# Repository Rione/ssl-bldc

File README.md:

# Ri-one BLDC Driver V1

|  | IC |
| --- | --- |
| MOSFET | [SIZ254DT-T1-GE3](https://www.mouser.jp/ProductDetail/Vishay-Siliconix/SIZ254DT-T1-GE3?qs=pUKx8fyJudCKVjpWQE2G2A%3D%3D) |
| MCU | [STM32F446RET6](https://jp.rs-online.com/web/p/microcontrollers/1106621) |
| Gate Driver | [DVR8300DRGER](https://www.ti.com/product/DRV8300/part-details/DRV8300DRGER) |
| CAN Transceiver | [TJA1441AT](https://akizukidenshi.com/catalog/g/gI-17464/) |
| Shunt Resistor| 10mΩ | 
| 3.3V Regulator | [AP7333-33SAG](https://akizukidenshi.com/catalog/g/gI-11360/) |
| Motor | [EC 45 flat 30W](https://www.maxongroup.com/medias/sys_master/root/8846629470238/20-JP-285.pdf)|

---

初めて作ったモータドライバ基板です．
記事も書いたので，良かったら見てください．
[tomixrm 初のモタドラ設計！！ゲート抵抗を計算して求めてみた](https://tomixrm.vercel.app/2e7cb67096e143f2a43334a63c00d47e)

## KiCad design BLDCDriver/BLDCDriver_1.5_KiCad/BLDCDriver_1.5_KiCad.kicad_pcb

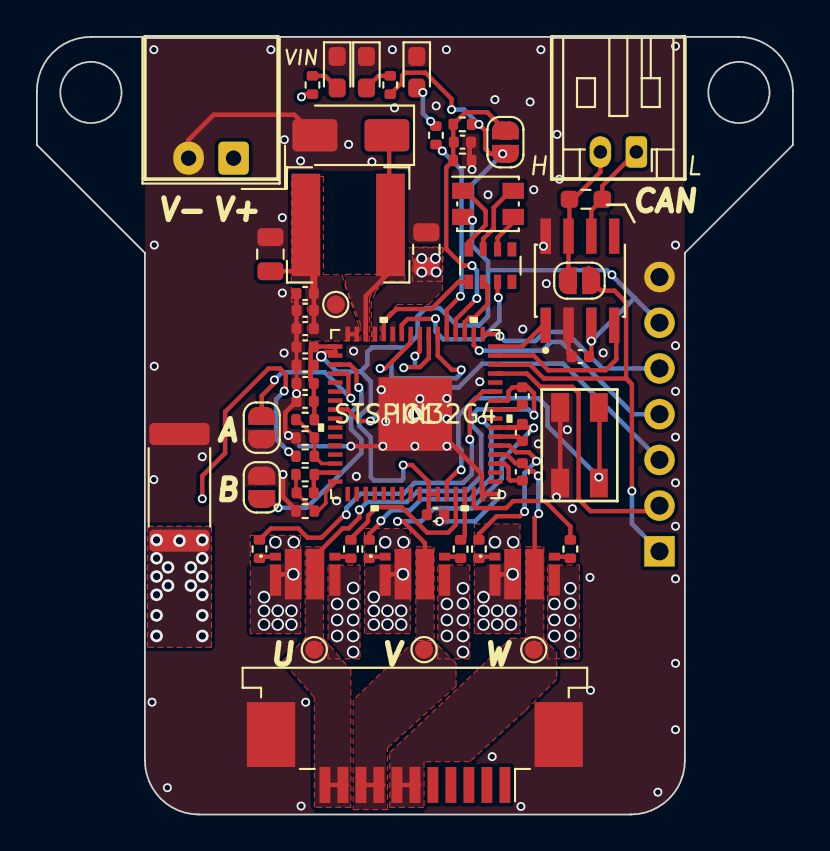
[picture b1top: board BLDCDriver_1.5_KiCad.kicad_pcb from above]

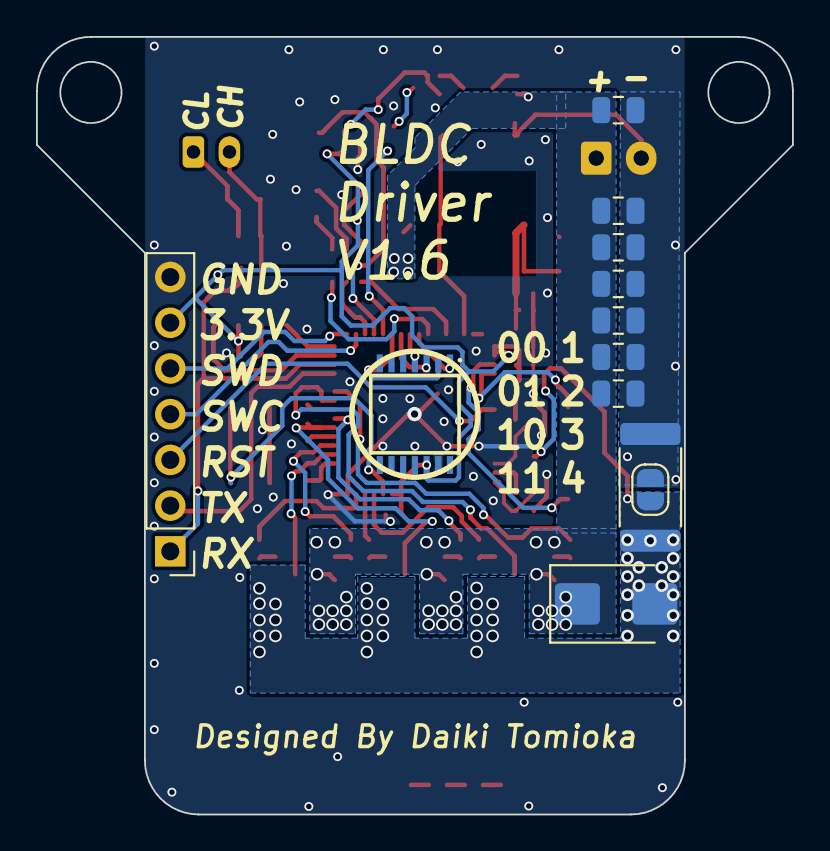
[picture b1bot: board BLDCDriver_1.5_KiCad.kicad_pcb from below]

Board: 2 copper layers, 42.0 x 43.2 mm, 70 parts (12 on the bottom side), 54 nets.

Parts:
C1, C2, C9, C17, C18, C19, C20: 22uF; C_0805_2012Metric
C3, C5, C7: 10uF; C_0402_1005Metric
C4, C6, C8, C25, C26: 100nF; C_0402_1005Metric
C10: 220nF; C_0805_2012Metric
C11, C12, C13, C14, C15, C16: 1uF; C_0402_1005Metric
C24: 10uf 25v; C_0805_2012Metric
D1: SS210; D_SMA
D2: LED_RGBA; LED_Kingbright_AAA3528ESGCT
D3: LED_Blue; LED_0603_1608Metric_Pad1.05x0.95mm_HandSolder
D4: LED_Pink; LED_0603_1608Metric_Pad1.05x0.95mm_HandSolder
D5: LED_White; LED_0603_1608Metric_Pad1.05x0.95mm_HandSolder
IC1: STSPIN32G4
J2: Debug; PinHeader_1x07_P2.54mm_Vertical
J3: FFC_11P_1mm; TE_1-84952-1_1x11-1MP_P1.0mm_Horizontal
J4: POWER; Molex_SPOX_5268-02A_1x02_P2.50mm_Horizontal
J5: CAN; JST_PH_S2B-PH-K_1x02_P2.00mm_Horizontal
JP1, JP2, JP3, JP4, JP5: Jumper_2_Open; SolderJumper-2_P1.3mm_Open_RoundedPad1.0x1.5mm
L1: 18uh; L_Bourns-SRN6028
R1, R14, R15: 22k; R_0402_1005Metric
R2, R11: 10k; R_0402_1005Metric
R4, R5, R6, R7, R8, R9: 51; R_0402_1005Metric
R10, R19: 4mΩ; R_2512_6332Metric
R12, R13, R16: 1.5k; R_0402_1005Metric
R17, R18: 1k; R_0402_1005Metric
R20: 120; R_0603_1608Metric_Pad0.98x0.95mm_HandSolder
RN1: 1k; R_Array_Convex_4x0603
SW1: SW_Push; SKRPACE010
TP1, TP2, TP3, TP4: TestPoint_Small; TestPoint_Pad_D1.0mm
TVS1: 16V; D_SMB
U1, U2, U3: SIZ254DTT1GE3
U5: AS5048A-HTSP-500; AS5048A_SOP65P640X120-14N
U7: MAX3051ESA_; SOIC127P600X175-8N

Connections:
BOOT1: C11.2, IC1.41 (BOOT1)
BOOT2: C13.2, IC1.38 (BOOT2)
BOOT3: C14.2, IC1.35 (BOOT3)
CANH: J5.2, JP5.1 (A), R20.1, U7.7 (CANH)
CANL: J5.1, R20.2, U7.6 (CANL)
CAN_RD: IC1.47 (PA11), U7.4 (RXD)
CAN_TD: IC1.48 (PA12), U7.1 (TXD)
GHS1: IC1.43 (GHS1), R4.1
GHS2: IC1.40 (GHS2), R6.1
GHS3: IC1.37 (GHS3), R8.1
GLS1: IC1.29 (GLS1), R5.1
GLS2: IC1.30 (GLS2), R7.1
GLS3: IC1.31 (GLS3), R9.1
GND: C1.1, C2.1, C3.2, C4.2, C5.2, C6.2, C7.2, C8.2, C9.1, C10.1, C12.2, C15.1, C17.1, C18.1, C19.1, C20.1, C24.2, C25.2, C26.2, D1.2 (A), D3.1 (K), D4.1 (K), D5.1 (K), IC1.32 (PGND), IC1.59 (PB8), IC1.65 (VSS), J2.7, J3.MP (MountPin), J4.2, JP2.2 (B), JP3.2 (B), JP4.2 (B), R2.2, R10.1, R13.1, R15.2, R19.1, SW1.1, U5.13 (GND), U7.2 (GND), U7.8 (RS)
GVCC_SW: D1.1 (K), IC1.62 (SW), L1.1
LED_Alive: IC1.53 (PD2), R18.1
LED_B: IC1.60 (PB9), RN1.5 (R4.2)
LED_G: IC1.51 (PA15), RN1.6 (R3.2)
LED_R: IC1.58 (PB7), RN1.7 (R2.2)
unnamed: D2.3 (BK), RN1.2 (R2.1)
unnamed: D2.2 (GK), RN1.3 (R3.1)
unnamed: D2.1 (RK), RN1.4 (R4.1)
unnamed: D3.2 (A), R11.2
unnamed: D4.2 (A), R17.2
unnamed: D5.2 (A), R18.2
unnamed: R4.2, U1.2 (G1)
unnamed: R5.2, U1.4 (G2)
unnamed: R6.2, U2.2 (G1)
unnamed: R7.2, U2.4 (G2)
unnamed: R8.2, U3.2 (G1)
unnamed: R9.2, U3.4 (G2)
OP_+1: IC1.14 (PA1), R12.2, R14.2, R15.1
OP_-1: C16.1, IC1.16 (PA3), R13.2, R16.1
OP_O1: C16.2, IC1.15 (PA2), R16.2
OUT1: C11.1, IC1.42 (OUT1), J3.10, J3.11, TP2.1, U1.3 (O)
OUT2: C13.1, IC1.39 (OUT2), J3.8, J3.9, TP3.1, U2.3 (O)
OUT3: C14.1, IC1.36 (OUT3), J3.6, J3.7, TP4.1, U3.3 (O)
SCREF: C12.1, IC1.52 (SCREF), JP1.1 (A), R1.2, R2.1
SHUNT_P1: JP2.1 (A), R10.2, R12.1, R19.2, TVS1.2 (A), U1.5 (S), U2.5 (S), U3.5 (S)
SPI1_CS: IC1.57 (PB6), U5.1 (~CSN)
SPI1_MISO: IC1.55 (PB4), U5.3 (MISO)
SPI1_MOSI: IC1.56 (PB5), U5.4 (MOSI)
SPI1_SCK: IC1.54 (PB3), U5.2 (CLK)
SW: IC1.28 (PB10), SW1.2
SWA: IC1.3 (PC13), JP3.1 (A)
SWB: IC1.4 (PC14), JP4.1 (A)
SWCLK: IC1.50 (PA14), J2.4
SWDIO: IC1.49 (PA13), J2.5
UART_RX: IC1.46 (PA10), J2.1, JP5.2 (B)
UART_TX: IC1.45 (PA9), J2.2
VCC: C7.1, C8.1, C24.1, C25.1, IC1.63 (VCC), IC1.64 (REGIN), L1.2, TP1.1
VD: C1.2, C2.2, C9.2, C10.2, C17.2, C18.2, C19.2, C20.2, IC1.61 (VM), J4.1, R11.1, TVS1.1 (K), U1.1 (D), U2.1 (D), U3.1 (D)
VDD: C3.1, C4.1, C5.1, C6.1, C15.2, C26.1, D2.4 (A), IC1.1 (REG3V3/VDD), IC1.2 (VBAT), IC1.26 (VREF+), IC1.27 (VDDA), J2.6, JP1.2 (B), R1.1, R14.1, R17.1, U5.12 (VDD3V), U7.3 (VCC)
nRST: IC1.8 (PG10), J2.3

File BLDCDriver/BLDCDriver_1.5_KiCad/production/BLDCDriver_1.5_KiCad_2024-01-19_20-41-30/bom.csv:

Designator,Footprint,Quantity,Value,LCSC Part #
"C1, C17, C18, C19, C2, C20, C9",0805,7,22uF,C338080
C10,0805,1,220nF,C107131
"C11, C12, C13, C14, C15, C16, C22",0402,7,1uF,C307413
"C21, C3, C5, C7",0402,4,10uF,C15525
"C23, C4, C6, C8",0402,4,100nF,C131394
C24,0805,1,10uf 25v,C15850
D1,D_SMA,1,SS210,C14996
D2,LED_Kingbright_AAA3528ESGCT,1,LED_RGBA,C2843813
D3,0603,1,LED_Blue,C965799
D4,0603,1,LED_Pink,C2977076
D5,0603,1,LED_White,C965808
IC1,STSPIN32G4,1,STSPIN32G4,C7434864
J2,PinHeader_1x07_P2.54mm_Vertical,1,Debug,
J3,TE_1-84952-1_1x11-1MP_P1.0mm_Horizontal,1,FFC_11P_1mm,C2914070
J4,Molex_SPOX_5268-02A_1x02_P2.50mm_Horizontal,1,POWER,
J5,JST_PH_S2B-PH-K_1x02_P2.00mm_Horizontal,1,CAN,C3021286
"JP1, JP2, JP3, JP4, JP5",SolderJumper-2_P1.3mm_Open_RoundedPad1.0x1.5mm,5,Jumper_2_Open,C20197
L1,L_Bourns-SRN6028,1,18uh,C467143
"R1, R14, R15",0402,3,22k,C325408
R10,2512,1,4mΩ,DNP
"R11, R2",0402,2,10k,C25744
"R12, R13, R16",0402,3,1.5k,C25867
"R17, R18",0402,2,1k,C11702
R19,2512,1,4mΩ,C5121077
R3,0603,1,120,C22787
"R4, R5, R6, R7, R8, R9",0402,6,51,C25125
RN1,R_Array_Convex_4x0603,1,1k,C20197
SW1,SKRPACE010,1,SW_Push,C3021286
"TP1, TP2, TP3, TP4",TestPoint_Pad_D1.0mm,4,TestPoint_Small,C22787
TVS1,D_SMB,1,16V,C25744
"U1, U2, U3",SIZ254DTT1GE3,3,~,C25768
U4,SOIC-8_3.9x4.9mm_P1.27mm,1,MCP2562-E-SN,C53609
U5,AS5048A_SOP65P640X120-14N,1,AS5048A-HTSP-500,
U6,AP7375-33SA-7_DIO,1,AP7375-50SA,C6500991

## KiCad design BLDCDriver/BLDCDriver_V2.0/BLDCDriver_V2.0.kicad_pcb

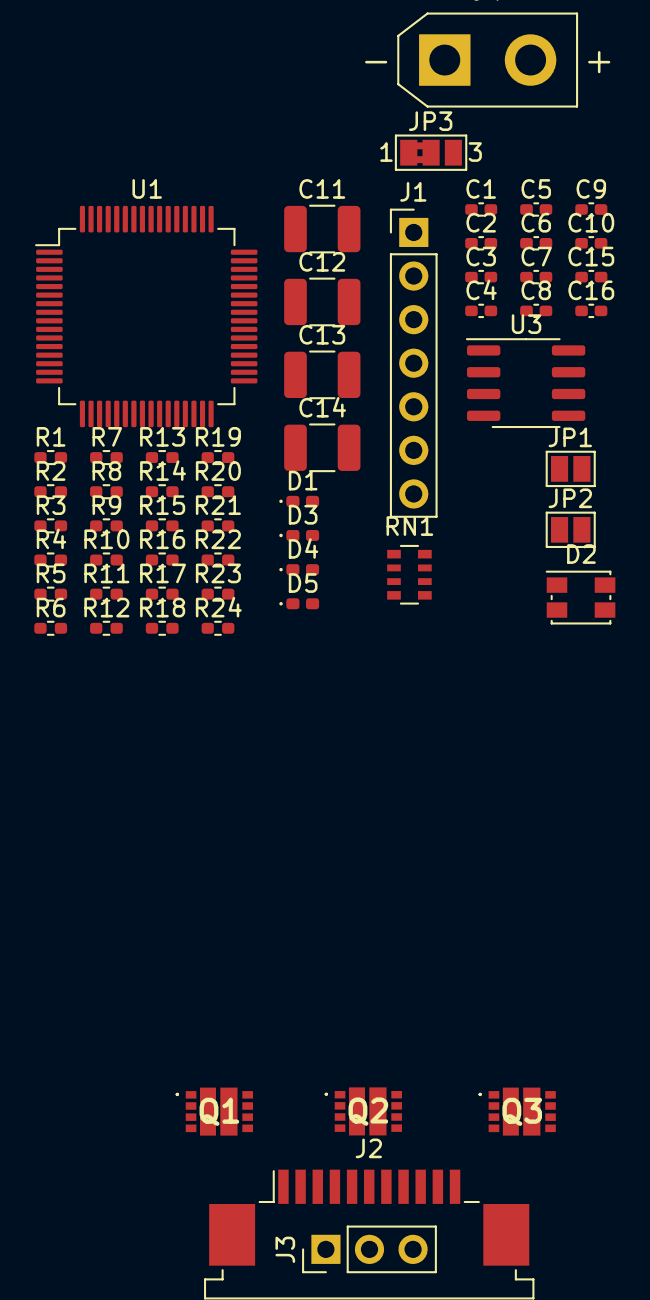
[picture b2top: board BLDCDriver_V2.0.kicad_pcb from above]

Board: 2 copper layers, 58 parts (0 on the bottom side), 49 nets, no tracks yet.

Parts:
C1, C2, C3, C4, C5, C7, C8, C9, C10, C15, C16: 0.1u; C_0402_1005Metric_Pad0.74x0.62mm_HandSolder
C6: 4.7u; C_0402_1005Metric_Pad0.74x0.62mm_HandSolder
C11, C12, C13, C14: 22u; C_1210_3225Metric_Pad1.33x2.70mm_HandSolder
D1, D3, D4, D5: LED; LED_0402_1005Metric_Pad0.77x0.64mm_HandSolder
D2: LED_RGBA; LED_Kingbright_AAA3528ESGCT
J1: STLink; PinHeader_1x07_P2.54mm_Vertical
J2: Motor Out; TE_1-84952-1_1x11-1MP_P1.0mm_Horizontal
J3: Conn_01x03; PinHeader_1x03_P2.54mm_Vertical
J4: PowerIN; AMASS_XT30UPB-F_1x02_P5.0mm_Vertical
JP1, JP2: Jumper_2_Open; SolderJumper-2_P1.3mm_Open_Pad1.0x1.5mm
JP3: Jumper_3_Bridged12; SolderJumper-3_P1.3mm_Bridged2Bar12_Pad1.0x1.5mm_NumberLabe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
Q1, Q2, Q3: SIZ254DT-T1-GE3; SIZ254DTT1GE3
R1, R2, R15, R16: 10k; R_0402_1005Metric_Pad0.72x0.64mm_HandSolder
R3, R4, R5, R6, R7, R8, R9, R17: 1k; R_0402_1005Metric_Pad0.72x0.64mm_HandSolder
R10, R11, R12, R13: 33k; R_0402_1005Metric_Pad0.72x0.64mm_HandSolder
R14: 120; R_0402_1005Metric_Pad0.72x0.64mm_HandSolder
R18: 50k; R_0402_1005Metric_Pad0.72x0.64mm_HandSolder
R19, R20, R21, R22, R23, R24: 51; R_0402_1005Metric_Pad0.72x0.64mm_HandSolder
RN1: 1k; R_Array_Convex_4x0603
U1: (symbol "Device:C" (pin_numbers hide) (pin_names 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; LQFP-64_10x10mm_P0.5mm
U3: MCP2562-E-SN; SOIC-8_3.9x4.9mm_P1.27mm

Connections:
+3.3V: D2.4 (A), J1.1, U3.5 (Vio)
+3V3: C1.1, C2.1, C3.1, C4.1, C5.1, C7.1, C15.1, R1.1, R3.1
+5V: C16.1, U3.3 (VDD)
+BATT: C11.1, C12.1, C13.1, C14.1, J4.1, JP3.1 (A), Q1.2 (D), Q2.2 (D), Q3.2 (D), R15.1
CANH: R14.1, U3.7 (CANH)
CANL: R14.2, U3.6 (CANL)
CANRX: U1.62 (PB9), U3.4 (RXD)
CANTX: U1.61 (PB8), U3.1 (TXD)
GND: C6.2, C11.2, C12.2, C13.2, C14.2, C15.2, C16.2, D1.1 (K), D3.1 (K), D4.1 (K), D5.1 (K), J1.2, J2.MP (MountPin), J4.2, JP1.2 (B), JP2.2 (B), Q1.5 (S), Q2.5 (S), Q3.5 (S), R2.1, R10.2, R11.2, R18.2, U1.12 (VSSA), U1.18 (VSS), U1.31 (VSS), U1.47 (VSS), U1.63 (VSS), U3.2 (VSS), U3.8 (STBY)
LED: R17.1, U1.3 (PC14)
LED_B: RN1.7 (R2.2), U1.34 (PB13)
LED_G: RN1.6 (R3.2), U1.36 (PB15)
LED_R: RN1.5 (R4.2), U1.35 (PB14)
unnamed: C2.2, U1.19 (VDD)
unnamed: C3.2, U1.32 (VDD)
unnamed: C4.2, U1.48 (VDD)
unnamed: C5.2, U1.64 (VDD)
unnamed: D1.2 (A), R3.2
unnamed: D2.3 (BK), RN1.2 (R2.1)
unnamed: D2.2 (GK), RN1.3 (R3.1)
unnamed: D2.1 (RK), RN1.4 (R4.1)
unnamed: D3.2 (A), R15.2
unnamed: D4.2 (A), R16.2
unnamed: D5.2 (A), R17.2
unnamed: Q1.1 (G1), R19.2
unnamed: Q1.8 (G2), R20.2
unnamed: Q2.1 (G1), R21.2
unnamed: Q2.8 (G2), R22.2
unnamed: Q3.1 (G1), R23.2
unnamed: Q3.8 (G2), R24.2
unnamed: R2.2, U1.60 (BOOT0)
unnamed: R1.2, U1.7 (NRST)
unnamed: C1.2, U1.1 (VBAT)
unnamed: C6.1, U1.30 (VCAP_1)
unnamed: C7.2, U1.13 (VDDA)
unnamed: R6.2, R12.1
unnamed: R7.2, R10.1
unnamed: R8.2, R13.1
unnamed: R9.2, R11.1
U: C8.1, Q3.10 (O), R4.2, R6.1
UOut: J2.7, J2.8, J3.1, R4.1, R7.1
USBRX: J1.6, U1.17 (PA3)
V: C9.1, Q2.10 (O)
VDD: JP3.2 (C), JP3.3 (B), R16.1
VOut: J2.9, J2.10, J3.2
W: C10.1, Q1.10 (O), R5.2, R8.1
WOut: J2.11, J3.3, R5.1, R9.1
modeA: JP1.1 (A), U1.59 (PB7)
modeB: JP2.1 (A), U1.57 (PB5)

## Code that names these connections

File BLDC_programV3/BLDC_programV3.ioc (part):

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Mcu.Name=STM32G431V(6-8-B)Tx
Mcu.Package=LQFP100
Mcu.UserName=STM32G431VBTx
PA1.Mode=Standalone
PA1.Signal=OPAMP1_VINP
PA10.Mode=Asynchronous
PA10.Signal=USART1_RX
PA11.Mode=FDCAN_Activate
PA11.Signal=FDCAN1_RX
PA12.Mode=FDCAN_Activate
PA12.Signal=FDCAN1_TX
PA13.Mode=Serial_Wire
PA13.Signal=SYS_JTMS-SWDIO
PA14.Mode=Serial_Wire
PA14.Signal=SYS_JTCK-SWCLK
PA15.GPIOParameters=GPIO_Label
PA15.GPIO_Label=LED_G
PA15.Signal=GPIO_Output
PA2.Signal=SharedAnalog_PA2
PA3.Mode=Standalone
PA3.Signal=OPAMP1_VINM
PA9.Mode=Asynchronous
PA9.Signal=USART1_TX
PB0.Mode=Standalone
PB0.Signal=OPAMP3_VINP
PB1.Signal=SharedAnalog_PB1
PB10.GPIOParameters=GPIO_PuPd,GPIO_Label
PB10.GPIO_Label=SW
PB10.GPIO_PuPd=GPIO_PULLUP
PB10.Signal=GPIO_Input
PB2.Mode=Standalone
PB2.Signal=OPAMP3_VINM
PB3.Mode=Full_Duplex_Master
PB3.Signal=SPI1_SCK
PB4.Mode=Full_Duplex_Master
PB4.Signal=SPI1_MISO
PB5.Mode=Full_Duplex_Master
PB5.Signal=SPI1_MOSI
PB6.GPIOParameters=GPIO_Label
PB6.GPIO_Label=SPI1_NSS
PB6.Signal=GPIO_Output
PB7.GPIOParameters=GPIO_Label
PB7.GPIO_Label=LED_R
PB7.Signal=GPIO_Output
PB9.GPIOParameters=GPIO_Label
PB9.GPIO_Label=LED_B
PB9.Signal=GPIO_Output
PC13.GPIOParameters=GPIO_PuPd,GPIO_Label
PC13.GPIO_Label=SW_A
PC13.GPIO_PuPd=GPIO_PULLUP
PC13.Signal=GPIO_Input
PC14-OSC32_IN.GPIOParameters=GPIO_PuPd,GPIO_Label
PC14-OSC32_IN.GPIO_Label=SW_B
PC14-OSC32_IN.GPIO_PuPd=GPIO_PULLUP
PC14-OSC32_IN.Signal=GPIO_Input
PC6.GPIOParameters=GPIO_Label
PC6.GPIO_Label=LED
PC6.Signal=GPIO_Output
PC8.Mode=I2C
PC8.Signal=I2C3_SCL
PC9.Mode=I2C
PC9.Signal=I2C3_SDA
PD2.GPIOParameters=GPIO_Label
PD2.GPIO_Label=LED_ALIVE
PD2.Signal=GPIO_Output
PE10.GPIOParameters=GPIO_Label
PE10.GPIO_Label=INL2
PE10.Mode=PWM Generation2 CH2 CH2N
PE10.Signal=TIM1_CH2N
PE11.GPIOParameters=GPIO_Label
PE11.GPIO_Label=INH2
PE11.Signal=S_TIM1_CH2
PE12.GPIOParameters=GPIO_Label
PE12.GPIO_Label=INL3
PE12.Mode=PWM Generation3 CH3 CH3N
PE12.Signal=TIM1_CH3N
PE13.GPIOParameters=GPIO_Label
PE13.GPIO_Label=INH3
PE13.Signal=S_TIM1_CH3
PE14.GPIOParameters=GPIO_PuPd,GPIO_Label
PE14.GPIO_Label=READY
PE14.GPIO_PuPd=GPIO_PULLUP
PE14.Signal=GPIO_Input
PE15.GPIOParameters=GPIO_PuPd,GPIO_Label
PE15.GPIO_Label=NFAULT
PE15.GPIO_PuPd=GPIO_PULLUP
PE15.Signal=GPIO_Input
PE7.GPIOParameters=GPIO_Label
PE7.GPIO_Label=WAKE
PE7.Signal=GPIO_Output
PE8.GPIOParameters=GPIO_Label
PE8.GPIO_Label=INL1
PE8.Mode=PWM Generation1 CH1 CH1N
PE8.Signal=TIM1_CH1N
PE9.GPIOParameters=GPIO_Label
PE9.GPIO_Label=INH1
PE9.Signal=S_TIM1_CH1
RCC.HSE_VALUE=16000000
RCC.SYSCLKFreq_VALUE=170000000
RCC.SYSCLKSource=RCC_SYSCLKSOURCE_PLLCLK
board=custom

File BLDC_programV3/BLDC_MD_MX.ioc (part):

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Mcu.Name=STM32F446R(C-E)Tx
Mcu.Package=LQFP64
Mcu.UserName=STM32F446RETx
PA0-WKUP.GPIOParameters=GPIO_Label
PA0-WKUP.GPIO_Label=C_U
PA0-WKUP.Signal=GPIO_Analog
PA1.GPIOParameters=GPIO_Label
PA1.GPIO_Label=C_W
PA1.Signal=GPIO_Analog
PA13.Mode=Serial_Wire
PA13.Signal=SYS_JTMS-SWDIO
PA14.Mode=Serial_Wire
PA14.Signal=SYS_JTCK-SWCLK
PA2.GPIOParameters=GPIO_Label
PA2.GPIO_Label=USBTX
PA2.Mode=Asynchronous
PA2.Signal=USART2_TX
PA3.GPIOParameters=GPIO_Label
PA3.GPIO_Label=USBRX
PA3.Mode=Asynchronous
PA3.Signal=USART2_RX
PA4.Mode=NSS_Signal_Hard_Output
PA4.Signal=SPI1_NSS
PA5.Mode=Full_Duplex_Master
PA5.Signal=SPI1_SCK
PA6.Mode=Full_Duplex_Master
PA6.Signal=SPI1_MISO
PA7.Mode=Full_Duplex_Master
PA7.Signal=SPI1_MOSI
PB10.GPIOParameters=GPIO_Label
PB10.GPIO_Label=PWM_C
PB10.Signal=S_TIM2_CH3
PB13.GPIOParameters=GPIO_Label
PB13.GPIO_Label=BLUE
PB13.Signal=GPIO_Output
PB14.GPIOParameters=GPIO_Label
PB14.GPIO_Label=RED
PB14.Signal=GPIO_Output
PB15.GPIOParameters=GPIO_Label
PB15.GPIO_Label=GREEN
PB15.Signal=GPIO_Output
PB4.GPIOParameters=GPIO_Label
PB4.GPIO_Label=PWM_B
PB4.Signal=S_TIM3_CH1
PB5.GPIOParameters=GPIO_Label
PB5.GPIO_Label=IDIN_B
PB5.Signal=GPIO_Input
PB6.GPIOParameters=GPIO_Label
PB6.GPIO_Label=SPI1_CS
PB6.Signal=GPIO_Output
PB7.GPIOParameters=GPIO_Label
PB7.GPIO_Label=IDIN_A
PB7.Signal=GPIO_Input
PB8.Mode=CAN_Activate
PB8.Signal=CAN1_RX
PB9.Mode=CAN_Activate
PB9.Signal=CAN1_TX
PC13.Signal=GPIO_Input
PC14-OSC32_IN.GPIOParameters=GPIO_Label
PC14-OSC32_IN.GPIO_Label=LED
PC14-OSC32_IN.Signal=GPIO_Output
PC7.GPIOParameters=GPIO_Label
PC7.GPIO_Label=PWM_A
PC7.Signal=S_TIM3_CH2
RCC.SYSCLKFreq_VALUE=180000000
RCC.SYSCLKSource=RCC_SYSCLKSOURCE_PLLCLK
board=custom

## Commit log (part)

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2022-10-15 set limitation of velocity at 100
2022-10-15 gitignore
2022-10-15 add lib
2022-10-15 achieve to turn a motor on STM32
    lib_archive = falseをするとplatoformIOのSTM32duinoがちゃんと動いてくれる
2022-10-16 add schematic
2022-10-18 gitignore : support ignore Eagle cashfile
2022-10-18 add MOSFETs on driver schematic
2022-11-04 ゲートドライバを50Ωに決定した
    詳しくは https://www.notion.so/rionessl/MOSFET-c3f0bc53d559421c83d572cacaf1d697#0553bd1ca6b7412ab2f7f6d7e1a45fa8
2022-11-05 CurrentSenseを追加した
2022-11-05 STM32と磁気エンコーダを追加した
2022-11-05 somefix
    # ==== Emojis ====
    # ✨ :sparkles: Add new feature
    # ✅ :white_check_mark: Update existing feature (not bug)
    # ⚠️ :warning: Fix bug/error
    # 🔥 :fire: Remove files or features
    # ✏️ :pencil2: Fix typos
2022-11-06 自分、泣いていいすか
2022-11-06 救いはないんですか〜？
    # ==== Emojis ====
    # ✨ :sparkles: Add new feature
    # ✅ :white_check_mark: Update existing feature (not bug)
    # ⚠️ :warning: Fix bug/error
    # 🔥 :fire: Remove files or features
    # ✏️ :pencil2: Fix typos
2022-11-07 ちょっと頑張った
    # ==== Emojis ====
    # ✨ :sparkles: Add new feature
    # ✅ :white_check_mark: Update existing feature (not bug)
    # ⚠️ :warning: Fix bug/error
    # 🔥 :fire: Remove files or features
    # ✏️ :pencil2: Fix typos
2022-11-08 モータ固定台のシルク入れた
    # ==== Emojis ====
    # ✨ :sparkles: Add new feature
    # ✅ :white_check_mark: Update existing feature (not bug)
    # ⚠️ :warning: Fix bug/error
    # 🔥 :fire: Remove files or features
    # ✏️ :pencil2: Fix typos
2022-11-08 シャント抵抗を裏側にした。GVDD消した
    # ==== Emojis ====
    # ✨ :sparkles: Add new feature
    # ✅ :white_check_mark: Update existing feature (not bug)
    # ⚠️ :warning: Fix bug/error
    # 🔥 :fire: Remove files or features
    # ✏️ :pencil2: Fix typos
2022-11-08 気合いが足りない。
    # ✨ :sparkles: Add new feature
    # ✅ :white_check_mark: Update existing feature (not bug)
    # ⚠️ :warning: Fix bug/error
    # 🔥 :fire: Remove files or features
    # ✏️ :pencil2: Fix typos
    # 📝 :memo: Update documentation
2022-11-09 CANに対応していき
    # ==== Emojis ====
    # ✨ :sparkles: Add new feature
    # ✅ :white_check_mark: Update existing feature (not bug)
    # ⚠️ :warning: Fix bug/error
    # 🔥 :fire: Remove files or features
    # ✏️ :pencil2: Fix typos
2022-11-09 ちょっと希望が見えた
2022-11-09 希望が見えてきた
2022-11-09 𝐏𝐎𝐖𝐄𝐑した
    # ==== Emojis ====
    # ✨ :sparkles: Add new feature
    # ✅ :white_check_mark: Update existing feature (not bug)
    # ⚠️ :warning: Fix bug/error
    # 🔥 :fire: Remove files or features
    # ✏️ :pencil2: Fix typos
2022-11-09 FETにビア通した
    # ==== Emojis ====
    # ✨ :sparkles: Add new feature
    # ✅ :white_check_mark: Update existing feature (not bug)
    # ⚠️ :warning: Fix bug/error
    # 🔥 :fire: Remove files or features
    # ✏️ :pencil2: Fix typos
2022-11-09 配線1からやり直し
    # ==== Emojis ====
    # ✨ :sparkles: Add new feature
    # ✅ :white_check_mark: Update existing feature (not bug)
    # ⚠️ :warning: Fix bug/error
    # 🔥 :fire: Remove files or features
    # ✏️ :pencil2: Fix typos
2022-11-09 配置プロった
    - コンデンサを追加した。
    - 電流センシングの相をVからWに変えた
    - パワーラインから配線はじめた
2022-11-09 いい感じ🦀
    # ==== Emojis ====
    # ✨ :sparkles: Add new feature
    # ✅ :white_check_mark: Update existing feature (not bug)
    # ⚠️ :warning: Fix bug/error
    # 🔥 :fire: Remove files or features
    # ✏️ :pencil2: Fix typos
2022-11-09 ゲートドライバ周りの配線全部終わらせた
    # ==== Emojis ====
    # ✨ :sparkles: Add new feature
    # ✅ :white_check_mark: Update existing feature (not bug)
    # ⚠️ :warning: Fix bug/error
    # 🔥 :fire: Remove files or features
    # ✏️ :pencil2: Fix typos
2022-11-10 CANの配線をした
    # ==== Emojis ====
    # ✨ :sparkles: Add new feature
    # ✅ :white_check_mark: Update existing feature (not bug)
    # ⚠️ :warning: Fix bug/error
    # 🔥 :fire: Remove files or features
    # ✏️ :pencil2: Fix typos
2022-11-10 電源ラインのパワみを増やした
    # ==== Emojis ====
    # ✨ :sparkles: Add new feature
    # ✅ :white_check_mark: Update existing feature (not bug)
    # ⚠️ :warning: Fix bug/error
    # 🔥 :fire: Remove files or features
    # ✏️ :pencil2: Fix typos
2022-11-11 DXFを復元した
2022-11-11 ⚡️電源周りの配線パワみ増した
2022-11-11 CANトランシーバーの近くにコンデンサつけた
2022-11-11 ボードをパネライズした
2022-11-11 位置合せピンを追加した
2022-11-11 パネライズアゲイン
2022-11-11 部品の数値を編集
    # ==== Emojis ====
    # ✨ :sparkles: Add new feature
    # ✅ :white_check_mark: Update existing feature (not bug)
    # ⚠️ :warning: Fix bug/error
    # 🔥 :fire: Remove files or features
    # ✏️ :pencil2: Fix typos
2022-11-13 発注します
    # ==== Emojis ====
    # ✨ :sparkles: Add new feature
    # ✅ :white_check_mark: Update existing feature (not bug)
    # ⚠️ :warning: Fix bug/error
    # 🔥 :fire: Remove files or features
    # ✏️ :pencil2: Fix typos
2022-11-13 発注したガーバーデータを追加した。
    # ==== Emojis ====
    # ✨ :sparkles: Add new feature
    # ✅ :white_check_mark: Update existing feature (not bug)
    # ⚠️ :warning: Fix bug/error
    # 🔥 :fire: Remove files or features
    # ✏️ :pencil2: Fix typos
2022-11-14 ステンシルデータを追加
    # ==== Emojis ====
    # ✨ :sparkles: Add new feature
    # ✅ :white_check_mark: Update existing feature (not bug)
    # ⚠️ :warning: Fix bug/error
    # 🔥 :fire: Remove files or features
    # ✏️ :pencil2: Fix typos
2022-11-15 change README.MD
    # ==== Emojis ====
    # ✨ :sparkles: Add new feature
    # ✅ :white_check_mark: Update existing feature (not bug)
    # ⚠️ :warning: Fix bug/error
    # 🔥 :fire: Remove files or features
    # ✏️ :pencil2: Fix typos
2022-11-15 BOMの作成
    # ==== Emojis ====
    # ✨ :sparkles: Add new feature
    # ✅ :white_check_mark: Update existing feature (not bug)
    # ⚠️ :warning: Fix bug/error
    # 🔥 :fire: Remove files or features
    # ✏️ :pencil2: Fix typos
2022-11-15 ゲート抵抗選定スクリプトの書き直し
2022-11-17 some fix README.MD
    ブログ記事のリンク載せた
2022-12-04 next
    # ==== Emojis ====
    # ✨ :sparkles: Add new feature
    # ✅ :white_check_mark: Update existing feature (not bug)
    # ⚠️ :warning: Fix bug/error
    # 🔥 :fire: Remove files or features
    # ✏️ :pencil2: Fix typos
2023-01-30 評価基板のアップデート
2023-03-10 fix position BST condenser
2023-04-22 create new program
2023-04-22 create new program BLDC_programV2
2023-04-22 エンコーダ原点と角速度のコードを修正
2023-04-22 limitを設けた
2023-04-22 clean files
2023-04-23 radianを使うように変更中
2023-04-23 モータドライバの故障診断プログラムを追加
2023-04-24 radianとdegreeの三角関数を作成
2023-04-25 PIDライブラリのエラーを修復
2023-04-25 abs,sqrt,atan2をMath.hに追加
2023-04-25 setPhaseVoltageにUdを追加，Diagnoseを変更中...
2023-04-25 センサードUqコントロールの検証(Diagnoseは一旦パス)
2023-04-25 速度PI制御に成功！！
2023-04-27 getTargetVelocityを追加
2023-05-02 some fix
2023-05-03 ドレミファソラシド
2023-05-27 :sparkles: version1.2完成(基板発注)
    # ==== Emojis ====
    # ✨ :sparkles: Add new feature
    # ✅ :white_check_mark: Update existing feature (not bug)
    # ⚠️ :warning: Fix bug/error
    # 🔥 :fire: Remove files or features
    # ✏️ :pencil2: Fix typos
2023-05-28 :sparkles: add CubeMX Project
    # ==== Emojis ====
    # ✨ :sparkles: Add new feature
    # ✅ :white_check_mark: Update existing feature (not bug)
    # ⚠️ :warning: Fix bug/error
    # 🔥 :fire: Remove files or features
    # ✏️ :pencil2: Fix typos
2023-05-28 :sparkles: generate PlatformIO Project form CubeMX
    # ==== Emojis ====
    # ✨ :sparkles: Add new feature
    # ✅ :white_check_mark: Update existing feature (not bug)
    # ⚠️ :warning: Fix bug/error
    # 🔥 :fire: Remove files or features
    # ✏️ :pencil2: Fix typos
2023-05-28 メモの追加
2023-05-29 :warning: CANTXとCANRXをスワップした
    # ==== Emojis ====
    # ✨ :sparkles: Add new feature
    # ✅ :white_check_mark: Update existing feature (not bug)
    # ⚠️ :warning: Fix bug/error
    # 🔥 :fire: Remove files or features
    # ✏️ :pencil2: Fix typos
2023-06-10 WIP CubeMX
    # ==== Emojis ====
    # ✨ :sparkles: Add new feature
    # ✅ :white_check_mark: Update existing feature (not bug)
    # ⚠️ :warning: Fix bug/error
    # 🔥 :fire: Remove files or features
    # ✏️ :pencil2: Fix typos
2023-06-10 :sparkles: add RGB Led
    # ==== Emojis ====
    # ✨ :sparkles: Add new feature
    # ✅ :white_check_mark: Update existing feature (not bug)
    # ⚠️ :warning: Fix bug/error
    # 🔥 :fire: Remove files or features
    # ✏️ :pencil2: Fix typos
2023-06-13 v1.4 test
    # ==== Emojis ====
    # ✨ :sparkles: Add new feature
    # ✅ :white_check_mark: Update existing feature (not bug)
    # ⚠️ :warning: Fix bug/error
    # 🔥 :fire: Remove files or features
    # ✏️ :pencil2: Fix typos
2023-06-19 :sparkles: create V2.0 in KiCAD7
    # ==== Emojis ====
    # ✨ :sparkles: Add new feature
    # ✅ :white_check_mark: Update existing feature (not bug)
    # ⚠️ :warning: Fix bug/error
    # 🔥 :fire: Remove files or features
    # ✏️ :pencil2: Fix typos
2023-10-04 プログラム忘れたけど，途中まで
    # ==== Emojis ====
    # ✨ :sparkles: Add new feature
    # ✅ :white_check_mark: Update existing feature (not bug)
    # ⚠️ :warning: Fix bug/error
    # 🔥 :fire: Remove files or features
    # ✏️ :pencil2: Fix typos
2023-10-04 :sparkles: V1.4 JLCPCBのPCBA検証用基板の設計DONE
    # ==== Emojis ====
    # ✨ :sparkles: Add new feature
    # ✅ :white_check_mark: Update existing feature (not bug)
    # ⚠️ :warning: Fix bug/error
    # 🔥 :fire: Remove files or features
    # ✏️ :pencil2: Fix typos
2023-12-14 基板生やした
2023-12-14 おそらくこれで速度司令を受けることができるようになった(未検証)
    0. ヘッダを受信
    1. vel[0]の 1byte目を受信
    2. vel[0]の 2byte目を受信
    3. vel[1]の 1byte目を受信
    4. vel[1]の 2byte目を受信
    5. vel[2]の 1byte目を受信
2023-12-26 unionだった
2023-12-27 ✨受信プログラムを修正！！
    手動でシリアル送るとうまく行くけど、Pythonで送るやつは上手く行ってない
2024-01-05 :sparkles: 無理やりフラッシュに書き込み読み出しができることが確認取れたが電源を切るとリセットされる
    リンカスクリプトを編集していないので。プログラムメモリと衝突していないのがラッキーぐらいの感覚で、危ないのでやめたほうがいい。一応成功しており、プログラムを書き換えてもデータを保持しているので成功している。
    EEPROMが乗らないのでFLASHに磁気エンコーダの値を書き込もうとしている。1万回程度で壊れるらしいが、書き込み回数より先にMDが壊れるだろうと思っている。
2024-01-06 ✨CubeMXでプロジェクト生成して、FLASH書き込み読み出しができたのと、AS5048Aを読み取れた
    - stm32pioでPlatformIOのプロジェクトに変更している
    - HAL_SPI_TransmitReceive_DMAで0xFFFFに投げて、その次に空データ送りつけて読み込みをDMAでやっている
    - DMA、めっちゃ複雑なんかと思ったけど、CubeMXでの設定はめっちゃ簡単だった。DMAと普通のやつの違いがよくわからん。DMAを使うとリングバッファ的なやつを作れるのかな。今回そんなことしてないけど。
    - DMAで16bit送るようにしているっぽい。できているのだろう。
    - AS5048Aを12bitと勘
2024-01-08 ✨PWM出力できた
    TIM1とTIM3を使って出力できた。1つのマイコンでBLDCを2つ回せるかも。
2024-01-11 ✨SerialをDMAで受信できた
    この後memsetなどを使ってfifoを実装する。
2024-01-11 ✨Serial Wrapperを書いた
    - 受信はDMAで
    - 送信は普通の送信
2024-01-11 ✨データ送信プロトコルでちゃんと受信できた
    0. ヘッダを受信
    1. vel[0]の 1byte目を受信
    2. vel[0]の 2byte目を受信
    3. vel[1]の 1byte目を受信
    4. vel[1]の 2byte目を受信
    5. vel[2]の 1byte目を受信
2024-01-11 ✨Serial,PWM,SPIを同時に宣言しても動いた
2024-01-11 ✨今のBLDCドライバようにプログラムを描き始めた
2024-01-11 ✨GPIOピンのラッパーが動いた
2024-01-12 ✨DWTを用いた実行時間計測用Timerクラスの実装完了
2024-01-12 ✨SPIのCSピンのON/OFFを1msから10nsに変更して1ループ20KHzにできた
2024-01-13 ✨CANでデータフレーム送信できた
    https://hsdev.co.jp/stm32-can/
    hcan1.Instance = CAN1;
    hcan1.Init.Prescaler = 5;
    hcan1.Init.Mode = CAN_MODE_NORMAL;
    hcan1.Init.SyncJumpWidth = CAN_SJW_1TQ;
    hcan1.Init.TimeSeg1 = CAN_BS1_6TQ;
2024-01-13 ✨CANの受信が確認できた
2024-01-13 🔥ゴミファイルを消した
2024-01-13 ✨CANのラッパー動いた
    受信割り込みでこの関数が呼び出されるので、オーバーロードする必要あり。
    void HAL_CAN_RxFifo0MsgPendingCallback(CAN_HandleTypeDef *hcan) {
    if (can.getHcan() == &hcan1) {
    can.recv(canRecvData);
    }
    }
2024-01-13 ✏️BLDCライブラリをIncludeしてコンパイルを通るようにした。
    次が処理の実装とかかな。
2024-01-14 ✨MKS CANable2.0(slcan)を使ってPython-canで送受信できた
2024-01-15 ✨FloatのPrintfに対応したはず
2024-01-15 ✨printf floatできた
    asm(".global _printf_float");
2024-01-16 ✨STSPIN32G4で基板設計を始めた
2024-01-18 ✨基板外形の更新と3Dデータのインポートをした
2024-01-18 ✨データシートを追加
2024-01-18 ✨回路を進めたよ。あとアートワーク太くするだけ。
    CANの電源が3.3Vだと厳しい印象。
2024-01-18 ✨DRCエラーを修正した
    MOSFETとゲート抵抗が近すぎると表示されるやつに関しては無視で行くしかない。
2024-01-18 ✨パワーラインのアートワークを仕上げた
    [-] GNDビア
    [-] CAN用LDO
2024-01-18 ✨ LED、LDO、ビアをやった
2024-01-19 ✨ID切り替えパッド、GNDベタ、パターン禁止エリア設定、テストポイント
    次は抵抗値の決定などをしていきたい。
2024-01-19 ✨sot23のSTEP読み込んだ
2024-01-19 ✨UARTで受信できる保険をかけた
2024-01-19 ⚠️PB8_BOOT0をGNDに落とした
    データシート読まないと...
2024-01-20 ✨Productionファイル生成した
2024-01-21 ⚠️電源のシルク逆、SPI_CS繋がってないのを修正、GNDベタ最適化、Production
    結構気づかなかったらやばかったやつばっかり
2024-01-25 ペリフェラルテスト開始
2024-01-25 ✨printfできた
    asm(".global _printf_float");
2024-01-25 ✨内蔵Flashにデータを書き込めました！！
    https://www.tomixrm.dev/STM32G431-Flash-HAL-7a6e0c2df70440688db178d7560de847
2024-01-26 ✨CAN通信できた。
    このサイトでCANのSample PointとボーレートからPrescalerの値などを出した。
    - 1000kBit/s
    - Sample Point 85%
    この2点を注意して以下のサイトでパラメータを計算させました。
    https://phryniszak.github.io/stm32g-fdcan/
2024-02-29 ✏️LEDのRGBの配線を修正・Lチカを確認・DCDCの出力にコンデンサを追加
2024-03-01 ✨PWM出力ができていることがわかったが、プロテクションが悪さをしておりまだモータ駆動はできていない。
2024-03-01 ✨MDで強制転流できたど〜〜〜〜！！！！
    RESETレジスタが大事だったっぽい。Device STATUS registerを眺めていたらモータが回る時と回らない時があって、見たらRESETレジスタだったので、操作したら動いた。
2024-03-22 ✨フットプリントをMAX3051に変更
2024-03-26 ✨LPF,PIDのライブラリを追加
2024-03-26 ✨エンコーダで読み取ってとりあえず回すやつできた
2024-03-26 ✏️ファイル分割をした
2024-03-27 ✨CANから目標速度を送って追従するように回すことができた

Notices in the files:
parts and their libraries:
Copyright 2021 Accelerated Designs. All rights reserved.
